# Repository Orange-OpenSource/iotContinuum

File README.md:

# IoT Continuum Development Kit

<picture>
 <source media="(prefers-color-scheme: dark)" srcset="images/devkit_general-white.png">
 <source media="(prefers-color-scheme: light)" srcset="images/devkit_general-black.png">
 
</picture>

## Why IoT Continuum

With IoT Continuum, gain in efficiency by capitalizing on everything that has been achieved in your project's previous development cycles. Thus, the components and the design used from the start-up phase (PoC – Proof of Concept) are scalable and compatible with the industrial deployment phase. A new design will therefore no longer be necessary either during the next phase of Proof Of Value (convincing) or in the final phase of deployment and industrial scale-up.

There are two models of Development Kit. 

One is based on an HL7812 LTE-M/NB-IoT cellular connectivity module and the next is based on an RC7620 LTE-Cat 1 module. Both of these modules are from SEMTECH.
This development kit is provided by IoT Continuum to developers who are willing to start from scratch with a development kit approved by IoT Continuum.

Read more on [IoT Continuum Website](https://iotjourney.orange.com/fr-FR/iotcontinuum)

## List of available Devkits. 

•	DEVKIT HL7812
All documentation and source code for the HL7812 Devkit are available from the IoT Continuum [HL7812 Devkit link](DevKit-HL7812/README.md).

•	DEVKIT RC7620
For the RC7620-based DevKit, the components are available from the IoT Continuum [RC7620 Devkit link](DevKit-RC7620).

# License

The content of this repository is provided by Orange SA under the [MIT license](/LICENSE).

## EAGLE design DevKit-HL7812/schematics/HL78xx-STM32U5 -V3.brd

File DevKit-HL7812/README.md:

# IoT Continuum Development Kit

<picture>
 <source media="(prefers-color-scheme: dark)" srcset="images/DevKit_face1-black.jpg">
 <source media="(prefers-color-scheme: light)" srcset="images/DevKit_face1-white.jpg">
 
</picture>

## Arduino IDE or STM32 Cube IDE?

2 Getting Started experiences are provided: one using the Arduino IDE (simpler) and the other one using the STM32 Cube IDE (recommended for proper engineering).

If you are discovering this development kit and are not familiar with STM32 Cube environment, we recommend you to [get started with the Arduino IDE](Arduino/README.md). Otherwise, the [STM32 Cube IDE](STM32Cube/) is the recommended way, especially because of its debug capabilities that are not available on Arduino environment.

## Specifications

<picture>
 <source media="(prefers-color-scheme: dark)" srcset="images/DevKit_face1-black-annotated.png">
 <source media="(prefers-color-scheme: light)" srcset="images/DevKit_face1-white-annotated.png">
 
</picture>

|  |  |
| --- | --- |
| **Microcontroller** | STM32U585CIU6 (STM32U5 series)  |
| Architecture | Ultra-low-power ARM Cortex-M33 32bits with FPU, DSP, MPU |
| Flash Memory | 2MBytes |
| SRAM | 786 KB |
| Clock Speed | 160 MHz |
| Compatibility | Arduino, STM32 |
|  |  |
| **Board** size | 72.66 x 38.1 mm |
| Operating Voltage | 3.3V |
| I/O Pins | 24 |
| Analog Output Pin | 12-bit DAC |
| External Interrupts | Available on all pins |
| DC Current per I/O pin | 5 mA |
| Power | 5V USB power and/or 3.7 LiPo battery |
| Charging | Charge controller, up to 500mA charge current with battery meter |
|  |  |
| **Sensors** |  |
| BME280 | Humidity, Pressure, Temperature sensors |
| LSM6DSOX | Accelerometer, Gyroscope |
| LED | RGB LED |
|  |  |
| **Connectivity** |  |
| Cellular Module | Sierra Wireless HL7812 |
| Cellular | LTE-M, 2G |
| Positioning | GNSS |
| USB | USB-C Port |

## Pinout

### Outer PINs

| I/O Pins | Arduino | STM32U585 |
| --- | --- | --- |
| 13 | IO13 | GPIO6 Expander |
| 12 | D12 | PB13 |
| 11 | D11 | PA11 |
| 10 | D10 | PA8 |
| 9 | D9 | PB15 |
| 6 | D6 | PB14 |
| 5 | D5 | PB10 |
| 4 | IO4 | GPIO1 Expander |
| SCL | D17 | PB6 |
| SDA | D18 | PB7 |
| RX/D1 | D1 | PA3 |
| TX/D0 | D0 | PA2 |
| A0 | A0/D2 | PA0 |
| A1 | A1/D3 | PA1 |
| A2 | A2/D4 | PA6 |
| A3 | A3/D7 | PB0 |
| A4 | A4/D8 | PB1 |
| A5 | A5/D13 | PB2 |
| SCK | D14 | PB3 |
| MISO | D15 | PB4 |
| MOSI | D16 | PB5 |

### Inner PINs

| I/O Pins | Arduino | STM32U585 | Comment |
| --- | --- | --- | --- |
| BAT_LEVEL | BAT_LEVEL | PA4 | Battery level |
| USB_UART_RX | PIN_SERIAL_RX | PA5 | RX to USB |
| USB_UART_TX | PIN_SERIAL_TX | PA7 | TX to USB |
| MODULE_TX | PIN_SERIAL3_TX | PA9 | TX to HL7812 |
| MODULE_RX | PIN_SERIAL3_RX | PA10 | RX to HL7812 |
| BUTTON | USER_BTN | PA12 | Push button status |
| SWDIO | NC | PA13 | J-TAG Programming |
| SWCLK | NC | PA14 | J-TAG Programming |
| WAKE_UP | WAKE_UP_HL7812 | PA15 | Module wake up on sleep |
| VGPIO | VGPIO | PC13 | Module state (active/on sleep) |
| SEL_MODE_UART | SWITCH_TO_HL7812 | PB8 | UART mode activation (STM32 or HL7812) |
| RESET MODULE | RESET_HL7812 | PB12 | Module Reset |
| INT2_ACCEL | INT_ACCEL | PB9 | LSM6DSOX interrupt state |
| LED RGB | RED_LED, GREEN_LED, BLUE_LED | NC | Led R=GPIO3, G=GPIO4, B=GPIO5 Expander |

# Development Environments

The IoT Continuum Development Kit is compatible with the following development environments:
* Arduino IDE: [Get started](Arduino/) -- recommended for a quick and easy start up
* STM32Cube IDE: [Get started](STM32Cube/) -- recommended for proper engineering (debug capabilities available)

# Firmware Upgrade

Check out the [Firmware Upgrade](Firmware_upgrade.md) section for upgrading the firmware of the various components of the Development Kit.

# Hardware Schematics

Hardware schematics are provided in [schematics](../schematics).

# License

The content of this repository is provided by Orange SA under the [MIT license](/LICENSE).

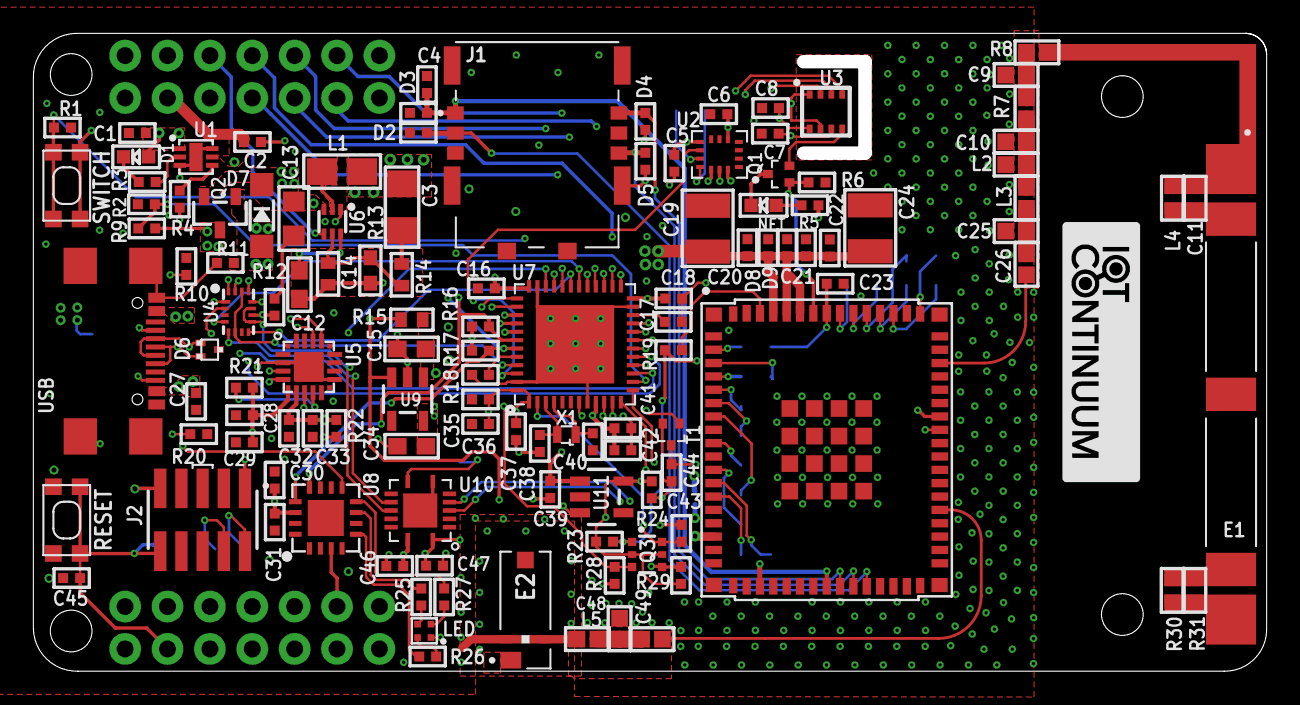
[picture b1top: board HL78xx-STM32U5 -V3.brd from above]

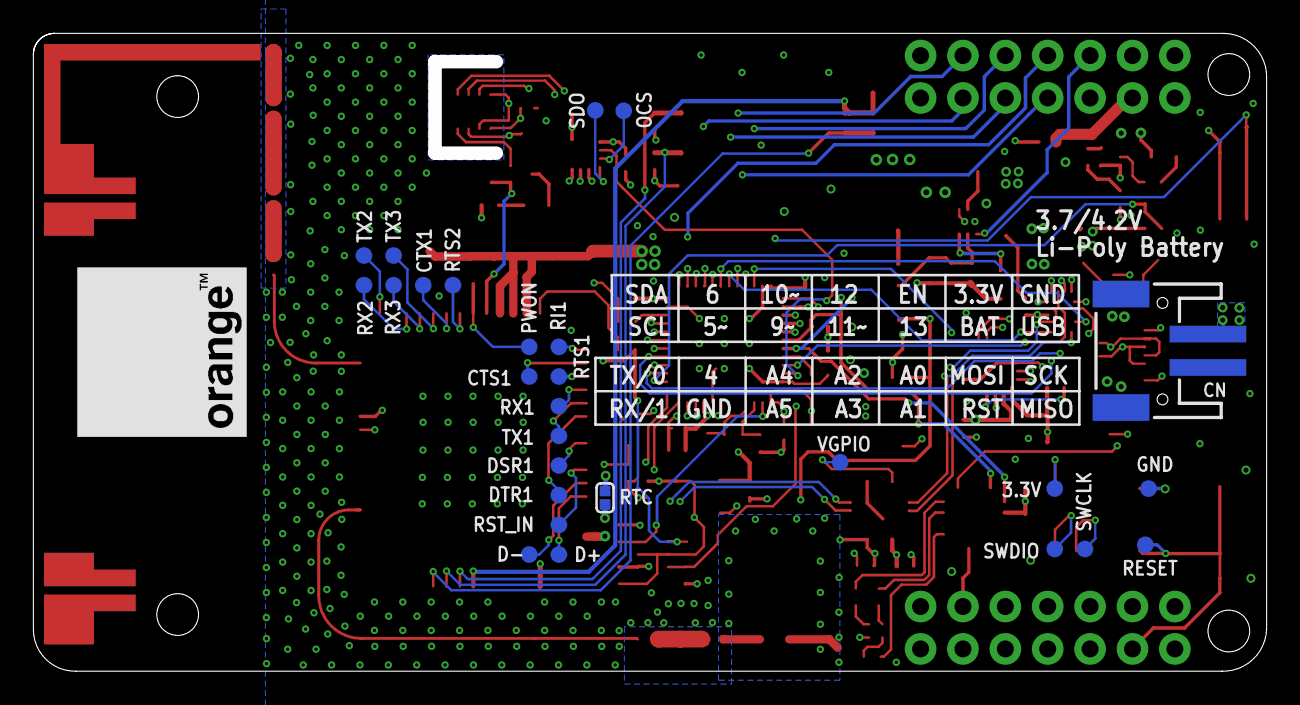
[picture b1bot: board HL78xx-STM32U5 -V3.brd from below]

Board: 6 copper layers, 73.9 x 38.2 mm, 149 parts (27 on the bottom side), 111 nets.

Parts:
3.3V: TP-1SIDE-1P0; TP-1P0
BOOTLOADER: SPST_TACT-KMR2; KMR2
C1, C2: 2.2uF; _0402
C3: 10uF; 1206
C4, C6, C7, C8, C12, C16, C18, C20, C28, C31, C33, C35, C39, C41, C43, C45, C46, C47: 100nF; _0402
C5, C27, C37, C42: 1uF; _0402
C9: 0.6pF; C_1MMX1MM-IGNION
C10: 2.1pF; C_1MMX1MM-IGNION
C11: 0.4pF; C_1MMX0.75MM-IGNION
C13: 15uF; _0805
C14: 120pF; 0402
C15, C34: 10uF; 0603
C17, C29, C32: 4.7uF; _0402
C19, C24: 150uF; 1210-C
C21: 10pF; _0402
C22, C23, C44: 33pF; _0402
C25: 1pF; C_1MMX1MM-IGNION
C26: 1.7pF; C_1MMX1MM-IGNION
C30, C36: 10uF; _0402
C38, C40: 12pF; _0402
C48: 0.1pF; C_1MMX1MM-IGNION
C49: 0.3pF; C_1MMX1MM-IGNION
CN: S2B-PH-SM4-TB(LF)(SN); JSTPH2
CTS1: TP-1SIDE-1P0; TP-1P0
CTX1: TP-1SIDE-1P0; TP-1P0
D1: ORANGE; CHIPLED_0603
D2, D3, D4, D5, D8, D9: CGA0402MLC-05G; _0402_ESD
D6: D_ESD5V3U2U-03F; SOT723
D7: SOD-123
D+: TP-1SIDE-1P0; TP-1P0
D-: TP-1SIDE-1P0; TP-1P0
DSR1: TP-1SIDE-1P0; TP-1P0
DTR1: TP-1SIDE-1P0; TP-1P0
E1: ANTENNA-FR01-S4-210; XDCR_FR01-S4-210
E2: NN03-320; XCVR_NN03-320
GND: TP-1SIDE-1P0; TP-1P0
H1, H2: HEADER2X7; 2X7-HEADER
J1: CONNECTORS_CON-SIM-104224-0820; CONNECTORS_MOLEX_104224-0820
J2: CON-FTSH-105-XX-X-DV; SAMTEC_FTSH-105-XX-X-DV
L1: 1uH (DFE201610E-1R0M=P2); 0806-IND
L2: 3.6nH; L_1MMX1MM-IGNION
L3: 3.7nH; L_1MMX1MM-IGNION
L4: 10nH; L_1MMX0.75MM-IGNION
L5: 1.5nH; L_1MMX1MM-IGNION
LED: LED-WURTH-150044M155260
NET: BLUE; CHIPLED_0603
OCS: TP-1SIDE-1P0; TP-1P0
PWON: TP-1SIDE-1P0; TP-1P0
Q1: NTA7002NT1G; SC-75/SOT-416
Q2: SI2101A-TP; SOT23-3
Q3: 2N7002DW-TP; SOT363
R1, R2, R9: 100K; 0402-R
R3, R5, R19, R21, R25, R26, R27: 1K; 0402-R
R4, R10, R20: 5.1K; 0402-R
R6, R11: 470K; 0402-R
R7, R8: 0R; R_1MMX1MM-IGNION
R12: 499K; 0603
R13: 523K; _0603-R
R14, R15: 100K; 0402
R16, R17, R18: 10K; 0402-R
R22: 2K2; 0402-R
R23, R24, R28, R29: 4.7K; 0402-R
R30, R31: 0R; R_1MMX0.75MM-IGNION
RESET: TP-1SIDE-1P0; TP-1P0
RI1: TP-1SIDE-1P0; TP-1P0
RST: SPST_TACT-KMR2; KMR2
RST_IN: TP-1SIDE-1P0; TP-1P0
RTC: SMT-JUMPER_2_NC_PASTE_SILK
RTS1, RTS2: TP-1SIDE-1P0; TP-1P0
RX1, RX2, RX3: TP-1SIDE-1P0; TP-1P0
SDO: TP-1SIDE-1P0; TP-1P0
SWCLK: TP-1SIDE-1P0; TP-1P0
SWDIO: TP-1SIDE-1P0; TP-1P0
T1: DTC114YE; SC-75/SOT-416
TX1, TX2, TX3: TP-1SIDE-1P0; TP-1P0
U1: SC810; MLPD-UT62X2
U2: LSM6DSOX; LGA-14L
U3: BME280; BME280_LGA
U4: DG2525; QFN-16L
U5: CP2102N-20; QFN20
U6: TPS62A02A; SOT-563
U7: STM32U585-QFN48; TQFN48_7MM
U8: PCA9534-PCA9534ARGVR; QFN16-4X4MM
U9: AP2112K-3.3; SOT23-5@1
U10: PVQFN-N14
U11: S1318; SOT23-5
U12: HL7812; HL781X
USB: USB4105-CGT
VGPIO: TP-1SIDE-1P0; TP-1P0
X1: ABS05-32.768KHZ-T; ABS05

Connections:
1.8V_EXT: C43.1, C47.2, Q3.2, Q3.5, R23.2, R29.2, U10.1, U11.5
3.3V: 3.3V.TP, BOOTLOADER.1, BOOTLOADER.3, C5.2, C6.2, C7.2, C8.2, C12.1, C16.1, C18.1, C28.1, C29.1, C30.1, C31.1, C34.2, C35.1, C36.1, C37.1, C41.1, C42.1, C46.1, H1.3, J2.1, LED.1, R5.1, R16.2, R17.2, R21.2, R24.2, R28.2, U2.5, U2.8, U2.12, U3.2, U3.6, U3.8, U4.10, U5.6, U7.1, U7.9, U7.24, U7.36, U7.48, U8.14, U9.5, U10.14
!POWER_ON_N: C23.1, PWON.TP, U12.C59
!RESET: C45.1, H2.4, J2.10, RESET.TP, RST.1, RST.3, U7.7
!RST_HL7812: C44.1, RST_IN.TP, T1.P3, U12.C11
A0: H2.5, U7.10
A1: H2.6, U7.11
A2: H2.7, U7.16
A3: H2.8, U7.18
A4: H2.9, U7.19
A5: H2.10, U7.20
AN: E2.4, L5.1
BAT_LEVEL: R2.1, R9.2, U7.14
BLUE: R27.2, U8.8
BOOT: R18.2, U7.44
BUTTON: BOOTLOADER.2, BOOTLOADER.4, R1.2, U7.33
CC1: R10.1, USB.A5
CC2: R20.1, USB.B5
CP2102_RX: U4.12, U5.17
CP2102_TX: U4.16, U5.18
CTS_HL7812: CTS1.TP, U12.C3
D4: H2.11, U8.3
D5: H1.12, U7.21
D6: H1.11, U7.27
D9: H1.10, U7.28
D10: H1.9, U7.29
D11: H1.8, U7.32
D12: H1.7, U7.26
D13: H1.6, U8.9
D+: D6.2, U5.4, USB.A6, USB.B6
D-: D6.1, U5.5, USB.A7, USB.B7
EN: H1.5, R15.2, U6.4, U9.3, U11.3
GND: C1.1, C2.1, C3.2, C4.2, C5.1, C6.1, C7.1, C8.1, C9.1, C10.1, C12.2, C13.2, C15.1, C16.2, C17.2, C18.2, C19.2, C20.2, C21.2, C22.2, C23.2, C24.2, C25.1, C27.1, C28.2, C29.2, C30.2, C31.2, C32.2, C33.2, C34.1, C35.2, C36.2, C37.2, C38.2, C39.2, C40.2, C41.2, C42.2, C43.2, C44.2, C45.2, C46.2, C47.1, C48.2, CN.1, D2.1, D3.1, D4.1, D5.1, D6.3, D8.1, D9.1, E2.2, GND.TP, H1.1, H2.12, J1.G1, J1.G2, J1.G3, J1.G4, J1.S4, J2.9, L2.2, Q1.P2, R1.1, R2.2, R4.1, R6.2, R10.2, R11.1, R14.1, R18.1, R20.2, RST.4, T1.P2, U1.3, U1.6, U1.THERMAL, U2.1, U2.2, U2.3, U2.6, U2.7, U3.1, U3.5, U3.7, U4.2, U5.3, U5.12, U5.TP, U6.1, U7.8, U7.23, U7.35, U7.47, U7.THERMAL, U8.1, U8.6, U8.15, U8.16, U8.T, U9.2, U10.6, U10.7, U10.9, U10.GND, U11.2, U12.C30, U12.C32, U12.C37, U12.C39, U12.C48, U12.C50, U12.CG1, U12.CG2, U12.CG3, U12.CG4, U12.G1, U12.G2, U12.G3, U12.G4, U12.G5, U12.G6, U12.G7, U12.G8, U12.G9, U12.G10, U12.G11, U12.G12, U12.G13, U12.G14, U12.G15, U12.G16, USB.A1B12, USB.B1A12, USB.N0, USB.N1, USB.N2, USB.N3
GREEN: R25.2, U8.7
HL7812_SHIFT_RX: U4.5, U4.15, U10.10
HL7812_SHIFT_TX: U4.9, U4.11, U10.11
HL_D+: D-.TP, U12.C12
HL_D-: D+.TP, U12.C13
INT2_ACCEL: U2.9, U7.46
MISO: H2.2, U7.40
MODULE_RX: U4.8, U7.31
MODULE_TX: U4.4, U7.30
MOSI: H2.3, U7.41
unnamed: D1.C, R3.1
unnamed: C14.1, R13.1, R14.2, U6.5
unnamed: C17.1, U7.22
unnamed: R12.1, U6.6
unnamed: NET.C, Q1.P3
unnamed: L1.1, U6.2
unnamed: NET.A, R5.2
unnamed: RX2.TP, U12.C54
unnamed: TX2.TP, U12.C52
unnamed: RX3.TP, U12.C55
unnamed: TX3.TP, U12.C56
unnamed: CTX1.TP, U12.C57
unnamed: RTS2.TP, U12.C58
unnamed: LED.4, R27.1
unnamed: C48.1, C49.2, L5.2
unnamed: E1.PORT1, R8.1
unnamed: C10.2, L2.1, L3.2, R7.2
unnamed: C9.2, R7.1, R8.2
unnamed: C25.2, C26.1, L3.1
unnamed: C11.2, E1.P1_1, L4.1
unnamed: C11.1, E1.P1_2, L4.2
unnamed: LED.3, R25.1
unnamed: R22.1, U5.8
unnamed: E1.P2_1, R30.1, R31.1
unnamed: LED.2, R26.1
unnamed: E1.P2_2, R30.2, R31.2
unnamed: RI1.TP, U12.C2
unnamed: DTR1.TP, U12.C7
unnamed: DSR1.TP, U12.C9
unnamed: RTC.2, U12.C21
unnamed: R3.2, U1.2
unnamed: R4.2, U1.4
NETLIGHT: Q1.P1, R6.1, U12.C60
OCS_AUX: OCS.TP, U2.10
OSC32K_IN: C38.1, U7.3, X1.B
OSC32K_OUT: C40.1, U7.4, X1.A
RED: R26.2, U8.5
RESET: R21.1, U5.9
RF_GNSS: C49.1, U12.C38
RF_LTE-M: C26.2, U12.C49
RST_MODULE: T1.P1, U7.25
RTS_HL7812: RTS1.TP, U12.C4
RX/D1: H2.14, U7.13
RX_HL7812: RX1.TP, U10.5, U12.C5
SCK: H2.1, U7.39
SCL: H1.14, R16.1, U2.13, U3.4, U7.42, U8.12
SDA: H1.13, R17.1, U2.14, U3.3, U7.43, U8.13
SDO_AUX: SDO.TP, U2.11
SEL12-34: U4.6, U4.14, U7.45
SIM_CLK: D4.2, J1.S3, U12.C27
SIM_DATA: D5.2, J1.S6, U12.C28
SIM_RST: D2.2, J1.S2, U12.C29
SIM_VCC: C4.1, D3.2, J1.S1, U12.C26
SWCLK: J2.4, SWCLK.TP, U7.37
SWDIO: J2.2, SWDIO.TP, U7.34
TX/D0: H2.13, U7.12
TX_HL7812: TX1.TP, U10.4, U12.C6
UIM1_DET: R19.1, U12.C64
USB_UART_RX: U4.1, U7.15
USB_UART_TX: U4.13, U7.17
VBAT: C2.2, CN.2, H1.4, Q2.3, R9.1, U1.5
VBUS: C1.2, C27.2, C32.1, C33.1, D1.A, D7.A, H1.2, Q2.1, R11.2, R22.2, U1.1, U5.7, U12.C16, USB.A4B9, USB.B4A9
VGPIO: Q3.1, R19.2, R23.1, U10.8, U12.C45, VGPIO.TP
VGPIO_SHIFT: Q3.6, R24.1, U7.2
VIN: C13.1, C15.2, C39.1, D7.C, Q2.2, R15.1, U6.3, U9.1, U11.1
VIN_3.7V: C3.1, C14.2, C19.1, C20.1, C21.1, C22.1, C24.1, D8.2, D9.2, L1.2, R12.2, R13.2, RTC.1, U12.C61, U12.C62, U12.C63
WAKEUP: Q3.4, R29.1, U12.C44
WAKEUP_SHIFT: Q3.3, R28.1, U7.38

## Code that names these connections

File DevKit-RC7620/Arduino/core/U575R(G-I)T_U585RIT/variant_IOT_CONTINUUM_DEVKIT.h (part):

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
// // Battery level
 #ifndef BAT_LEVEL
   #define BAT_LEVEL             A14
 #endif

 // Accelerator interrupt
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   #define RESET_HL7812          PB12
 #endif

 // VGPIO_SHIFT
 #ifndef VGPIO
   #define VGPIO                 PC13
 #endif

 #ifndef PIN_SPI_MOSI
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
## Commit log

2024-03-14 Add Zephyr BSP
2025-07-25 Add Devkit RC7620
2025-07-25 Change name folder Devkit-7620 to DevKit-7620-1
2025-07-25 change name DevKit-RC7620 Folder
2025-07-25 Change RC7620 path

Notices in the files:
DevKit-RC7620/Arduino/core/U575R(G-I)T_U585RIT/variant_IOT_CONTINUUM_DEVKIT.h:
Copyright (c) 2020, STMicroelectronics
All rights reserved.
This software component is licensed by ST under BSD 3-Clause license,
the "License"; You may not use this file except in compliance with the
License. You may obtain a copy of the License at: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
DevKit-HL7812/README.md:
License: MIT
parts and their libraries:
SparkFun-Jumpers: Licensing: Creative Commons ShareAlike 4.0 International - https://creativecommons.org/licenses/by-sa/4.0
